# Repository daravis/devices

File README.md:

# Daravis Devices Monorepo

This repository contains all of the open-source software and hardware that Daravis Devices creates, along with any supporting assets. Please see `COPYING.md` for the licensing terms.

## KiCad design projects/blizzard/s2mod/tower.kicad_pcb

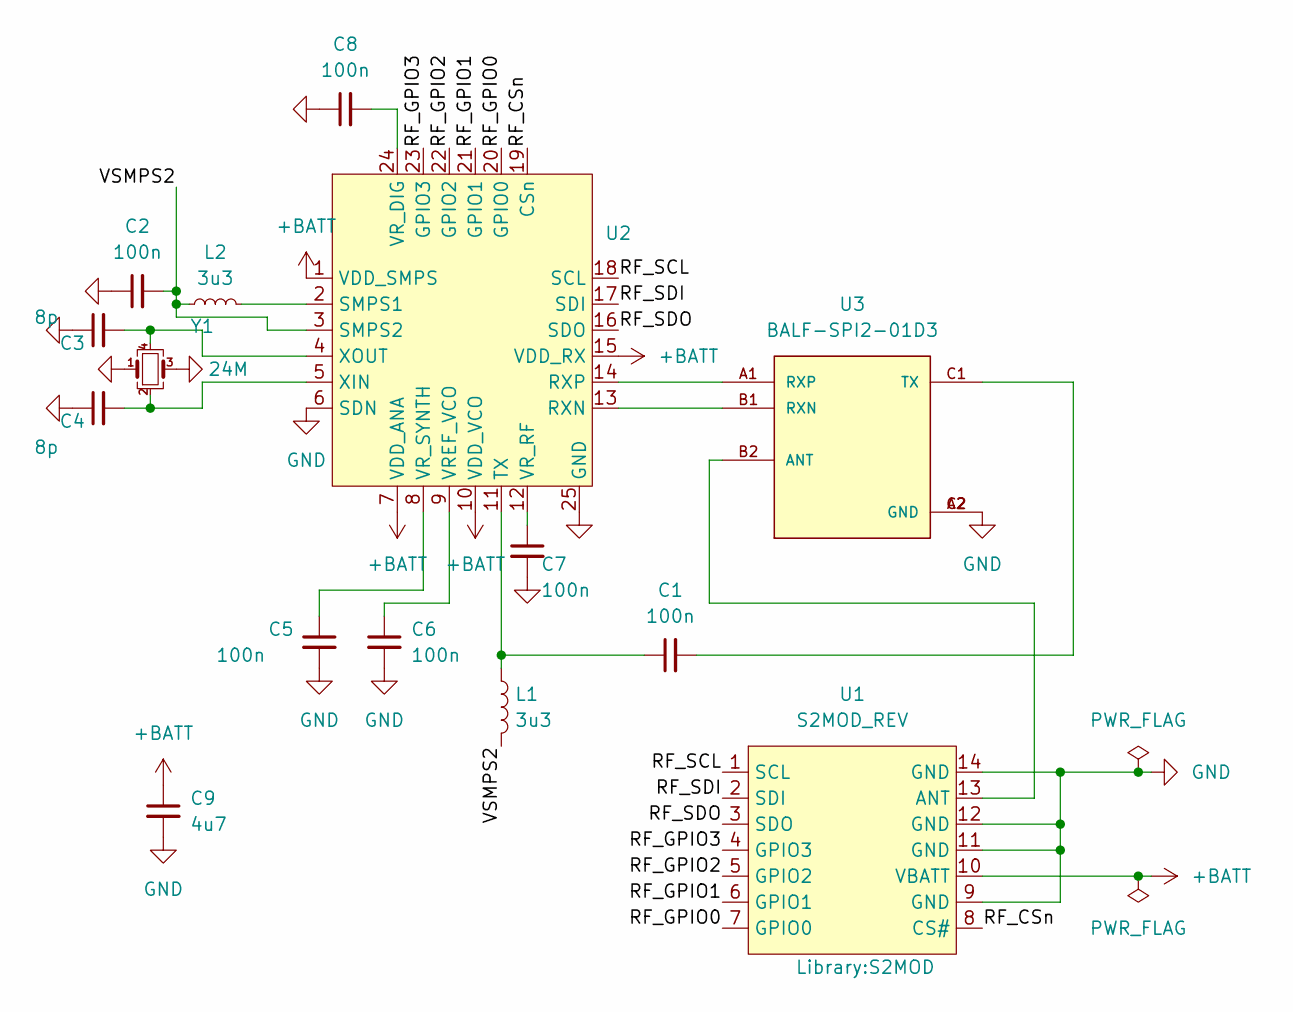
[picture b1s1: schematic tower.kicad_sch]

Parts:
C1, C2, C5, C6, C7, C8: 100n; C_0402_1005Metric; LCSC C307331
C3, C4: 8p; C_0402_1005Metric; LCSC C1578
C9: 4u7; C_0402_1005Metric; LCSC C23733
L1, L2: 3u3; L_0402_1005Metric; LCSC C84474
U1: S2MOD_REV; S2MOD
U2: VQFN-24-1EP_4x4mm_P0.5mm_EP2.5x2.5mm; LCSC C880591
U3: BALF-SPI2-01D3; XDCR_BALF-SPI2-01D3; PARTREV 2; JLCPCB_CORRECTION 0;0;-90
Y1: 24M; Crystal_SMD_2016-4Pin_2.0x1.6mm; LCSC C2929400

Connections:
+BATT: C9.1, U1.10 (VBATT), U2.1 (VDD_SMPS), U2.7 (VDD_ANA), U2.10 (VDD_VCO), U2.15 (VDD_RX)
/RF_CSn: U1.8 (CS#), U2.19 (CSn)
/RF_GPIO0: U1.7 (GPIO0), U2.20 (GPIO0)
/RF_GPIO1: U1.6 (GPIO1), U2.21 (GPIO1)
/RF_GPIO2: U1.5 (GPIO2), U2.22 (GPIO2)
/RF_GPIO3: U1.4 (GPIO3), U2.23 (GPIO3)
/RF_SCL: U1.1 (SCL), U2.18 (SCL)
/RF_SDI: U1.2 (SDI), U2.17 (SDI)
/RF_SDO: U1.3 (SDO), U2.16 (SDO)
/VSMPS2: C2.2, L1.2, L2.1, U2.3 (SMPS2)
GND: C2.1, C3.1, C4.1, C5.2, C6.2, C7.2, C8.1, C9.2, U1.9 (GND), U1.11 (GND), U1.12 (GND), U1.14 (GND), U2.6 (SDN), U2.25 (GND), U3.A2 (GND), U3.C2 (GND), Y1.1, Y1.3
unnamed: U1.13 (ANT), U3.B2 (ANT)
unnamed: U2.13 (RXN), U3.B1 (RXN)
unnamed: U2.14 (RXP), U3.A1 (RXP)
unnamed: L2.2, U2.2 (SMPS1)
unnamed: C1.1, L1.1, U2.11 (TX)
unnamed: C6.1, U2.9 (VREF_VCO)
unnamed: C8.2, U2.24 (VR_DIG)
unnamed: C7.1, U2.12 (VR_RF)
unnamed: C5.1, U2.8 (VR_SYNTH)
unnamed: C4.2, U2.5 (XIN), Y1.2
unnamed: C3.2, U2.4 (XOUT), Y1.4
unnamed: C1.2, U3.C1 (TX)

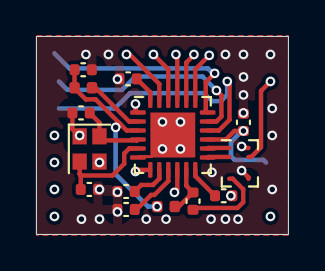
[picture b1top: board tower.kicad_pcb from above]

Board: 4 copper layers, 14.0 x 11.0 mm, 15 parts (0 on the bottom side), 23 nets.

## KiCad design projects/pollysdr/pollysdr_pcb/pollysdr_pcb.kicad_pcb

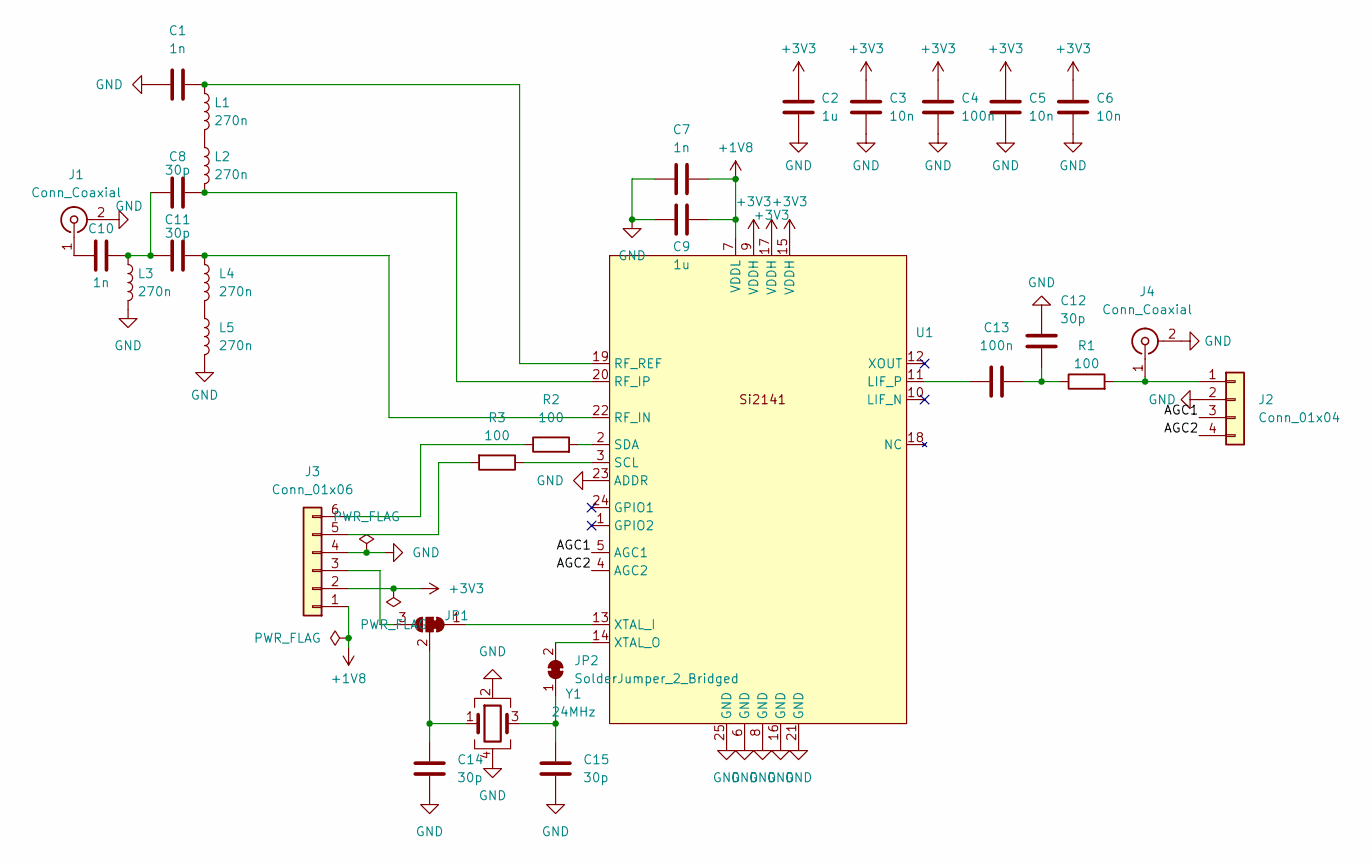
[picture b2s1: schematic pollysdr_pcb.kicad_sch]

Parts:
C1, C7, C10: 1n; C_0402_1005Metric
C2, C9: 1u; C_0402_1005Metric
C3, C5, C6: 10n; C_0402_1005Metric
C4, C13: 100n; C_0402_1005Metric
C8, C11, C12, C14, C15: 30p; C_0402_1005Metric
J1, J4: Conn_Coaxial; U.FL_Molex_MCRF_73412-0110_Vertical
J2: Conn_01x04; PinHeader_1x04_P2.54mm_Vertical
J3: Conn_01x06; PinHeader_1x06_P2.54mm_Vertical
JP1: SolderJumper_3_Bridged12; SolderJumper-3_P1.3mm_Bridged12_RoundedPad1.0x1.5mm_NumberL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
JP2: SolderJumper_2_Bridged; SolderJumper-2_P1.3mm_Bridged2Bar_RoundedPad1.0x1.5mm
L1, L2, L3, L4, L5: 270n; L_0402_1005Metric
R1, R2, R3: 100; R_0402_1005Metric
U1: SiliconLabs-QFN-24-1EP_3x3mm_P0.4mm_EP1.8x1.8mm
Y1: 24MHz; Crystal_SMD_2016-4Pin_2.0x1.6mm

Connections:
+1V8: C7.2, C9.2, J3.1, U1.7 (VDDL)
+3V3: C2.2, C3.1, C4.1, C5.1, C6.1, J3.2, U1.9 (VDDH), U1.15 (VDDH), U1.17 (VDDH)
/AGC1: J2.3, U1.5 (AGC1)
/AGC2: J2.4, U1.4 (AGC2)
GND: C1.1, C2.1, C3.2, C4.2, C5.2, C6.2, C7.1, C9.1, C12.1, C14.2, C15.2, J1.2 (Ext), J2.2, J3.4, J4.2 (Ext), L3.2, L5.2, U1.6 (GND), U1.8 (GND), U1.16 (GND), U1.21 (GND), U1.23 (ADDR), U1.25 (GND), Y1.2, Y1.4
unnamed: C8.1, C10.2, C11.2, L3.1
unnamed: C12.2, C13.2, R1.1
unnamed: C10.1, J1.1 (In)
unnamed: J2.1, J4.1 (In), R1.2
unnamed: J3.3, JP1.3 (B)
unnamed: J3.5, R3.2
unnamed: J3.6, R2.1
unnamed: JP1.1 (A), U1.13 (XTAL_I)
unnamed: C14.1, JP1.2 (C), Y1.1
unnamed: C15.1, JP2.1 (A), Y1.3
unnamed: JP2.2 (B), U1.14 (XTAL_O)
unnamed: L1.2, L2.1
unnamed: L4.2, L5.1
unnamed: C13.1, U1.11 (LIF_P)
unnamed: C11.1, L4.1, U1.22 (RF_IN)
unnamed: C8.2, L2.2, U1.20 (RF_IP)
unnamed: C1.2, L1.1, U1.19 (RF_REF)
unnamed: R3.1, U1.3 (SCL)
unnamed: R2.2, U1.2 (SDA)

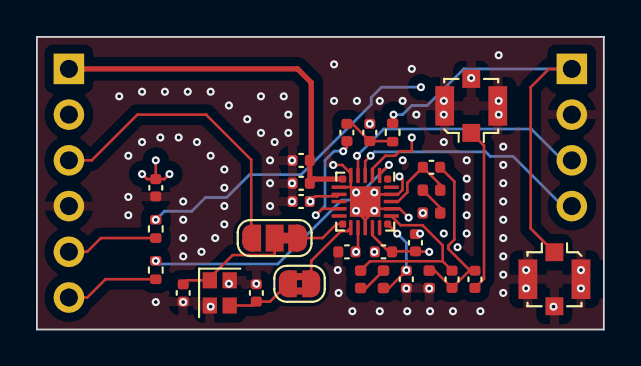
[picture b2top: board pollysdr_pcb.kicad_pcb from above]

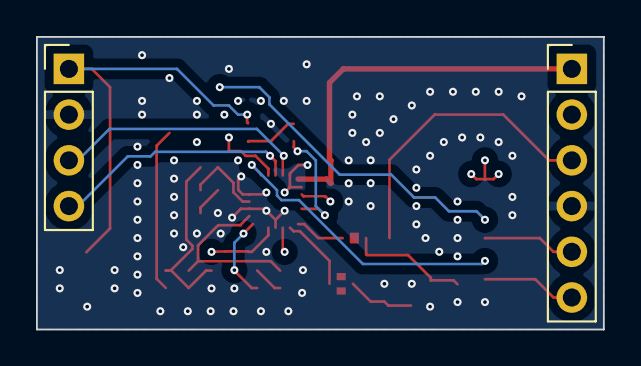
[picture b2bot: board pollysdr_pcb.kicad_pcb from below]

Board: 4 copper layers, 31.5 x 16.3 mm, 31 parts (2 on the bottom side), 24 nets.

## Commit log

2023-08-07 Update COPYING.md formatting
2023-09-04 Add a dummy board and some CI stuff for panelization
2023-09-05 Minor fixes to copying files, earthfile and add CI caching
2023-09-05 Correctly use inline caching
2023-09-05 Explicitly push kikit to cache
2023-09-05 Explicitly specify GHCR
2023-09-05 Actually generate drawings in the drawing generation workflow
2023-09-05 Add the SiLabs 3x3 QFN-24 footprint
2023-09-05 Add footprint and symbol for Si2141 based on data short
2023-09-05 Caching is hard and we'll deal with it later
2023-09-05 Check in a basic Si2141 breakout board. Untested.
2023-10-10 Add S2MOD board
2023-10-10 Update part number for inductors
2023-10-10 Fix balun rotation in JLCPCB exports
2023-10-11 Fix balun rotation in JLCPCB exports and change to LGA
